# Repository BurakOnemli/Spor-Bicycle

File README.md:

# Spor-Bicycle

My neighbour had a sports bicycle. Its paint was falling off and the screen was not working properly so I decided to renovate it. 
For project steps check wiki

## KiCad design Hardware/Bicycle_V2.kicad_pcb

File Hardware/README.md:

# Spor-Bicycle

My neighbour had a sport bicycle which's paint is falling off and the screen was not working properly so I dedided to renovate it. 

For detailed information please check the wiki.

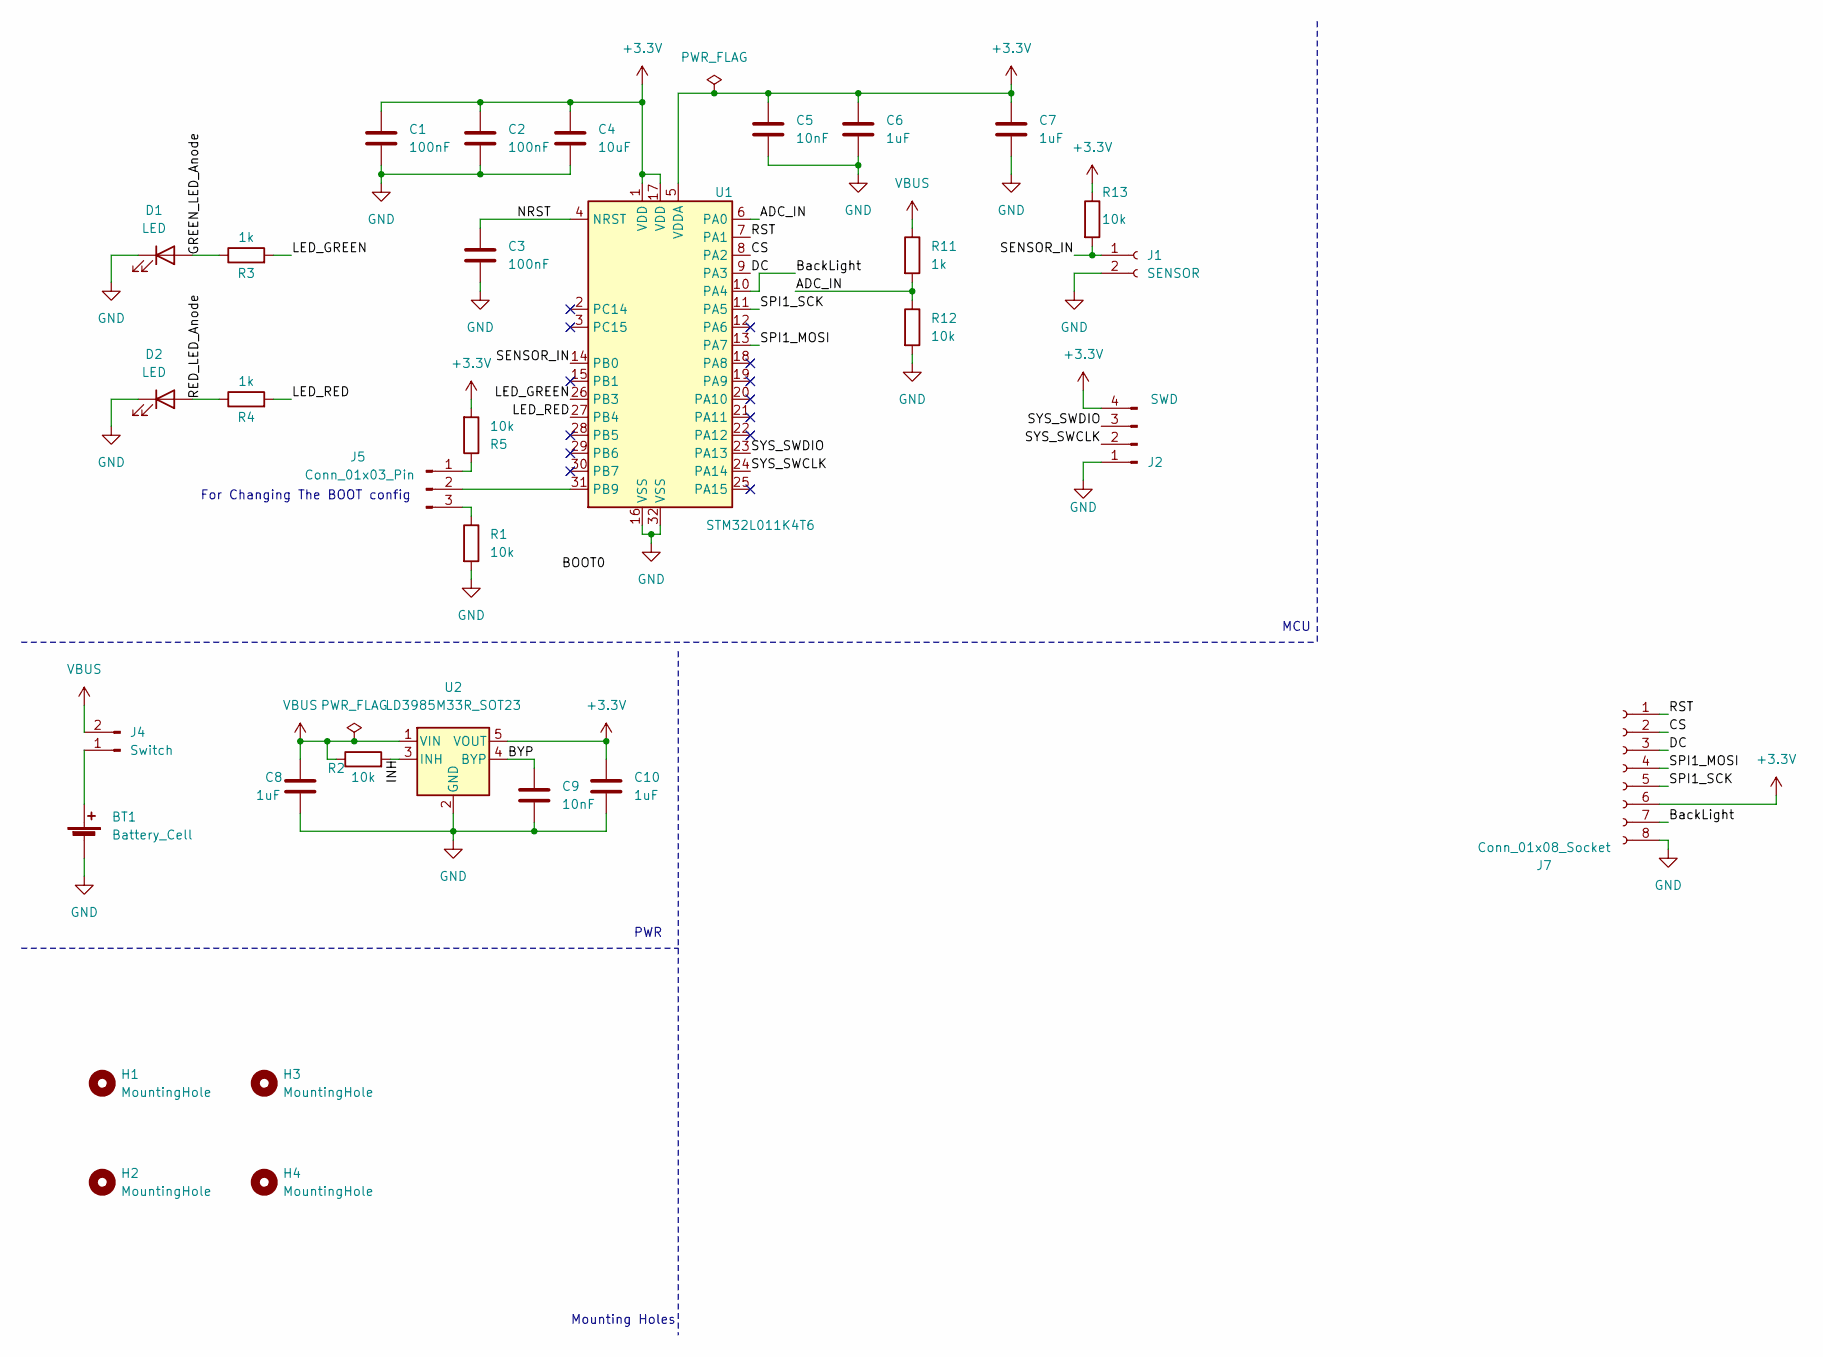
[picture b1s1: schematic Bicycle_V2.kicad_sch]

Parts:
BT1: Battery_Cell; BatteryHolder_MPD_BH-18650-PC2
C1, C2, C3: 100nF; C_0805_2012Metric
C4: 10uF; C_0805_2012Metric
C5, C9: 10nF; C_0805_2012Metric
C6, C7, C8, C10: 1uF; C_0805_2012Metric
D1, D2: LED; LED_D5.0mm
H1, H2, H3, H4: MountingHole; MountingHole_3.2mm_M3
J1: SENSOR; JST_EH_B2B-EH-A_1x02_P2.50mm_Vertical
J2: SWD; PinHeader_1x04_P2.54mm_Vertical
J4: Switch; PinHeader_1x02_P2.54mm_Vertical
J5: Conn_01x03_Pin; PinHeader_1x03_P2.54mm_Vertical
J7: Conn_01x08_Socket; PinSocket_1x08_P2.54mm_Vertical
R1, R2, R5, R12, R13: 10k; R_0805_2012Metric
R3, R4, R11: 1k; R_0805_2012Metric
U1: STM32L011K4T6; LQFP-32_7x7mm_P0.8mm
U2: LD3985M33R_SOT23; SOT-23-5

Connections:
+3.3V: C1.1, C2.1, C4.1, C5.1, C6.1, C7.1, C10.1, J2.4, J7.6, R5.2, R13.1, U1.1 (VDD), U1.5 (VDDA), U1.17 (VDD), U2.5 (VOUT)
/ADC_IN: R11.2, R12.1, U1.6 (PA0)
/BYP: C9.1, U2.4 (BYP)
/BackLight: J7.7, U1.10 (PA4)
/CS: J7.2, U1.8 (PA2)
/DC: J7.3, U1.9 (PA3)
/GREEN_LED_Anode: D1.2 (A), R3.1
/INH: R2.2, U2.3 (INH)
/LED_GREEN: R3.2, U1.26 (PB3)
/LED_RED: R4.2, U1.27 (PB4)
/NRST: C3.1, U1.4 (NRST)
/RED_LED_Anode: D2.2 (A), R4.1
/RST: J7.1, U1.7 (PA1)
/SENSOR_IN: J1.1, R13.2, U1.14 (PB0)
/SPI1_MOSI: J7.4, U1.13 (PA7)
/SPI1_SCK: J7.5, U1.11 (PA5)
/SYS_SWCLK: J2.2, U1.24 (PA14)
/SYS_SWDIO: J2.3, U1.23 (PA13)
GND: BT1.2 (-), C1.2, C2.2, C3.2, C4.2, C5.2, C6.2, C7.2, C8.2, C9.2, C10.2, D1.1 (K), D2.1 (K), J1.2, J2.1, J7.8, R1.2, R12.2, U1.16 (VSS), U1.32 (VSS), U2.2 (GND)
unnamed: BT1.1 (+), J4.1
unnamed: J5.1, R5.1
unnamed: J5.2, U1.31 (PB9)
unnamed: J5.3, R1.1
VBUS: C8.1, J4.2, R2.1, R11.1, U2.1 (VIN)

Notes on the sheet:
PWR
MCU
For Changing The BOOT config
Mounting Holes

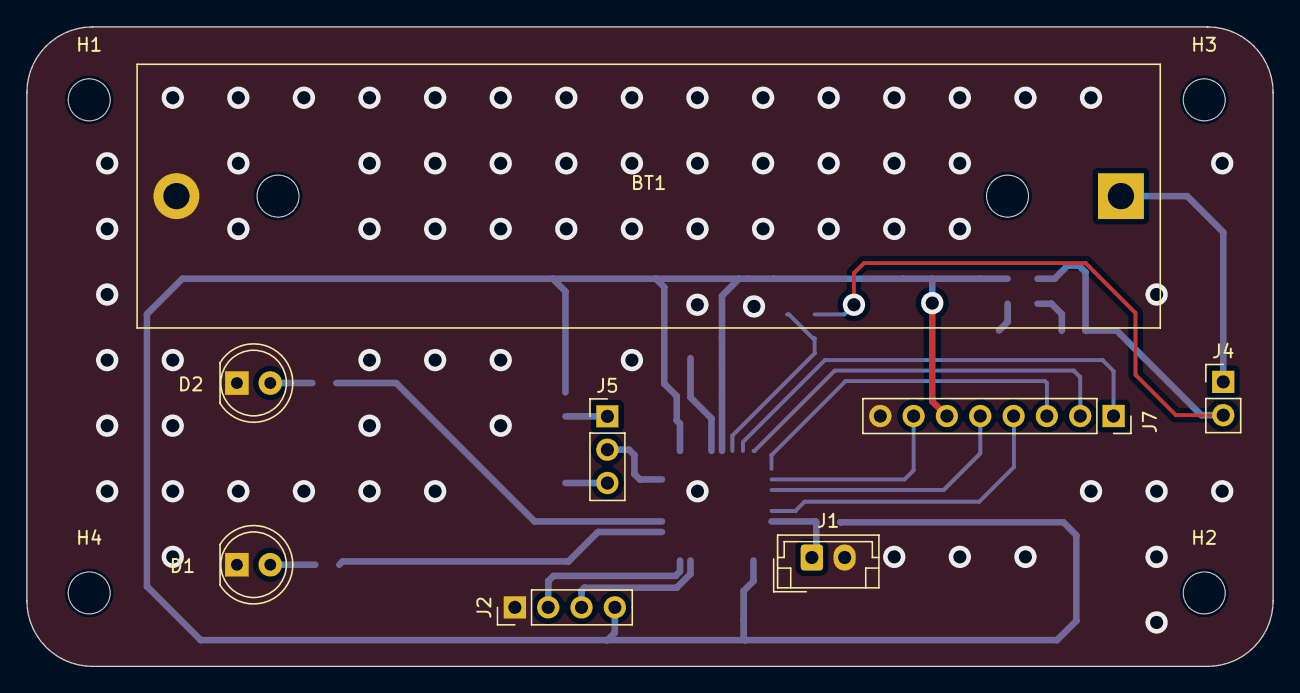
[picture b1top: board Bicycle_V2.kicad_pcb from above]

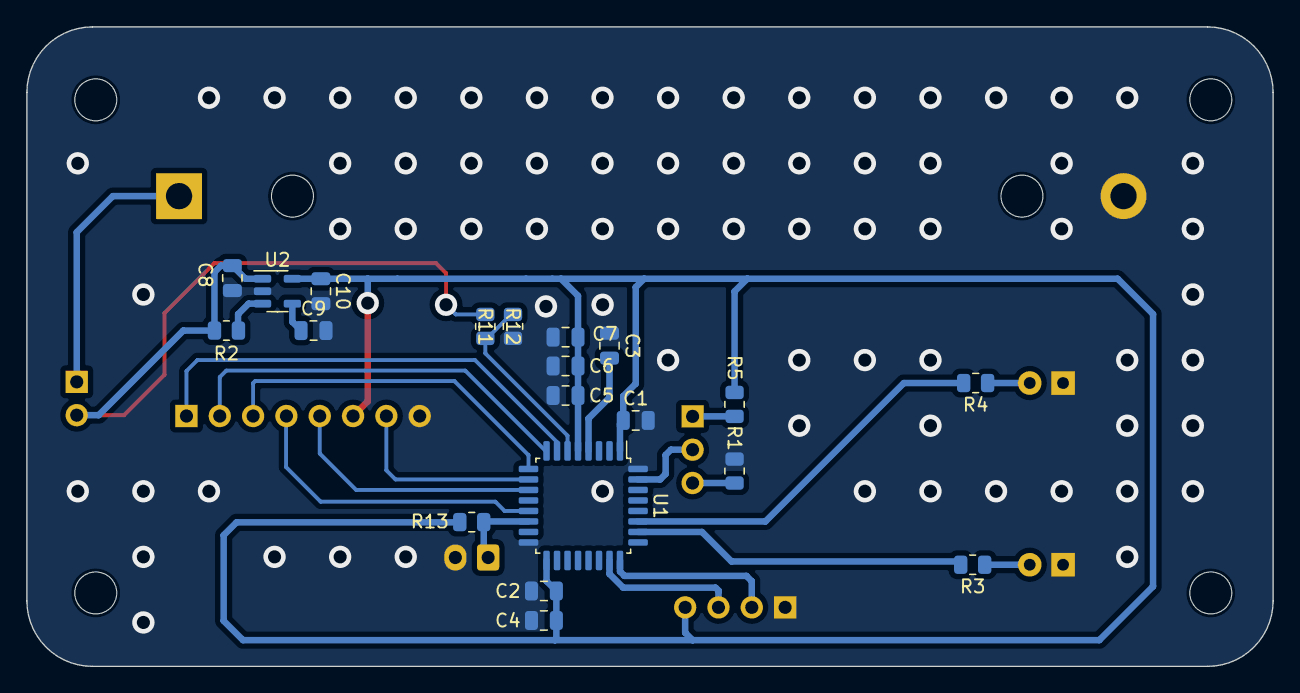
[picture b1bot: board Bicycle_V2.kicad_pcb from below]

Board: 2 copper layers, 95.0 x 48.8 mm, 32 parts (20 on the bottom side), 24 nets.

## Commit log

2023-02-19 Bicycle_Controller
2025-12-11 Latest Release
